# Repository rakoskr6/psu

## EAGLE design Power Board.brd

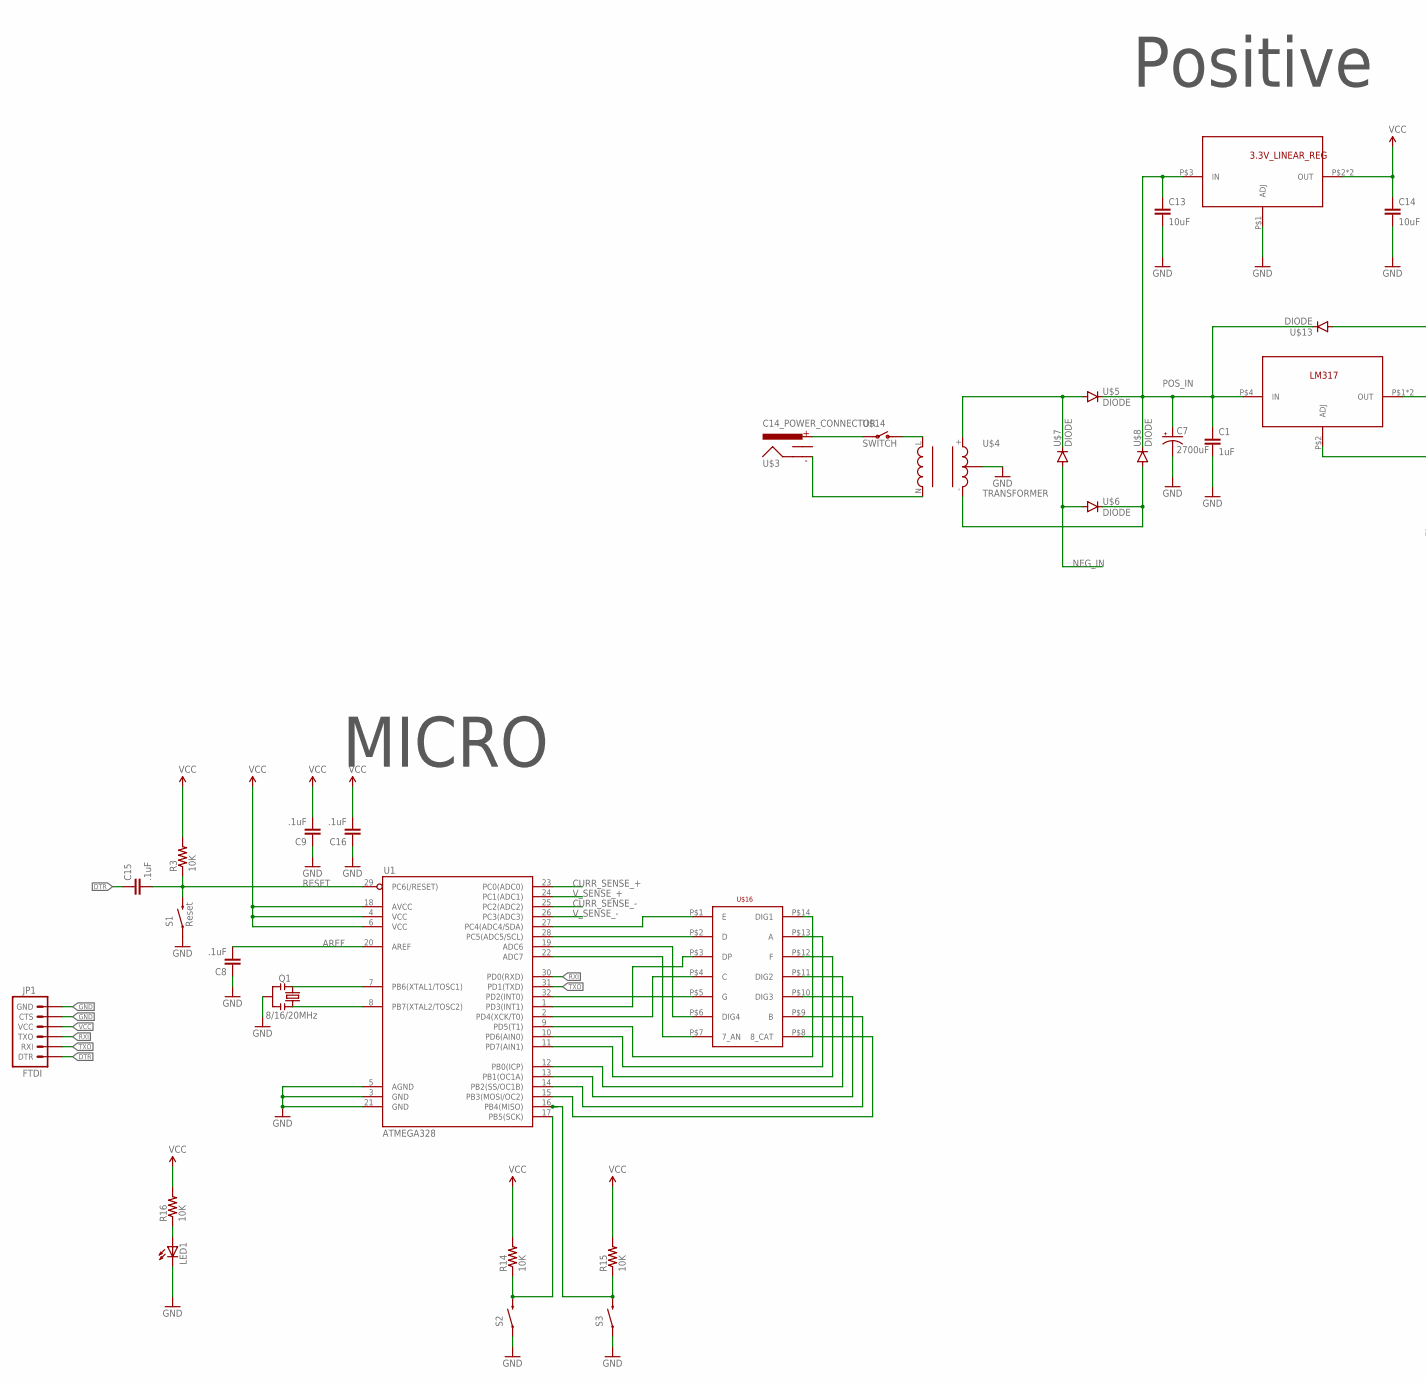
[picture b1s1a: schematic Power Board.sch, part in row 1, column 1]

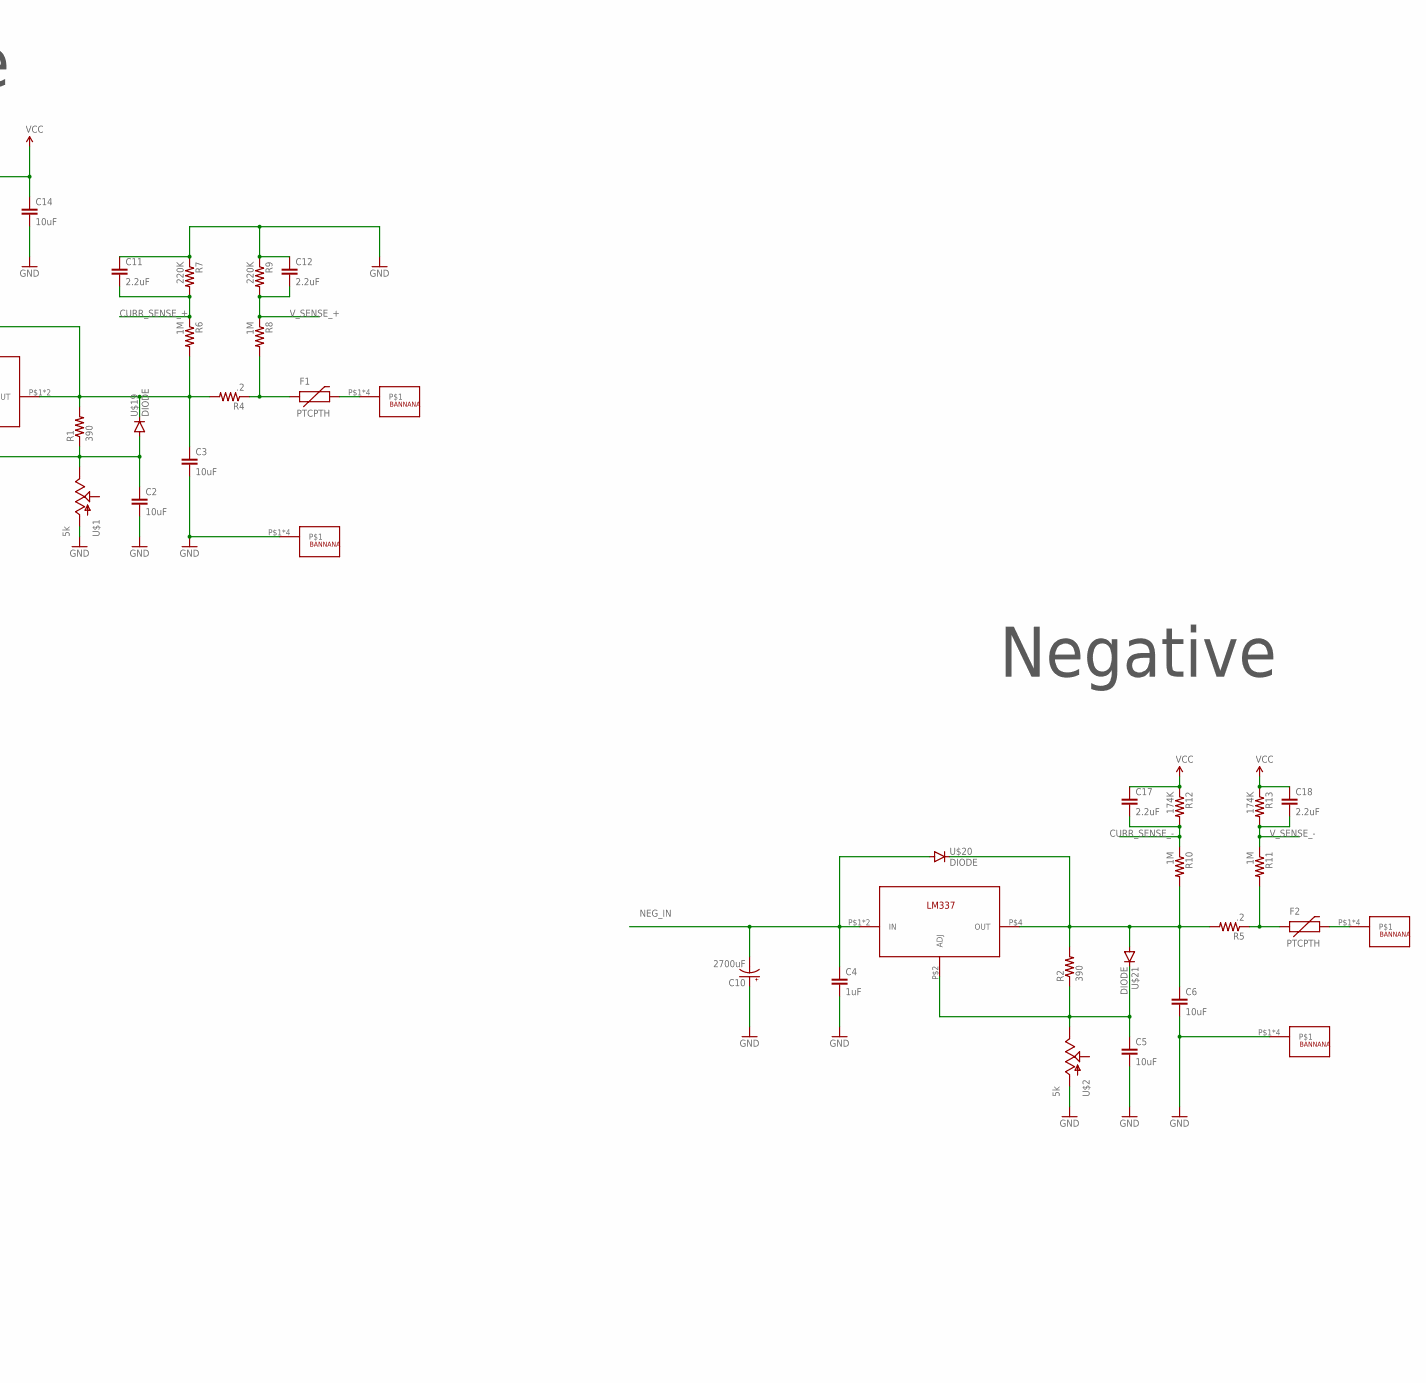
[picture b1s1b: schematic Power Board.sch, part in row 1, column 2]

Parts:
3.3V_LINEAR_REG: 3.3_LIN_REG; 3.3_LINEAR_REG
C1, C4: 1uF; 1206
C2, C3, C5, C6, C13, C14: 10uF; 1206
C7, C10: 2700uF; CPOL-RADIAL-1000UF-63V
C8, C9, C15, C16: .1uF; 1206
C11, C12, C17, C18: 2.2uF; 1206
F1, F2: PTCPTH; PTC
JP1: FTDI; 1X06
LED1: LED1206; LED-1206
LM317: LM317; KTT
LM337: LM337; KTT
NEG-GND: BANNANA
NEG-OUT: BANNANA
POS-GND: BANNANA
POS-OUT: BANNANA
Q1: 8/16/20MHz; RESONATOR-SMD-1:1
R1, R2: 390; 1206
R3, R14, R15, R16: 10K; 1206
R4, R5: .2; 1206
R6, R8, R10, R11: 1M; 1206
R7, R9: 220K; 1206
R12, R13: 174K; 1206
S1, S2, S3: Reset; TACTILE-SWITCH-SMD-ALT01
U1: ATMEGA328; TQFP32-08
U$1, U$2: 5k; POT
U$3: C14_POWER_CONNECTOR; PANEL_FOR_POWER
U$4: TRANSFORMER
U$5, U$6, U$7, U$8, U$13, U$19, U$20, U$21: DIODE
U$14: SWITCH
U$16: 4-DIGIT_7_SEG; 4-DIGIT_7-SEG

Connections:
3.3V: C17.1, C18.1, R12.1, R13.1, R15.2
AREF: C8.2, U1.20 (AREF)
CURR_SENSE_+: C11.2, R6.1, R7.2, U1.23 (PC0(ADC0))
CURR_SENSE_-: C17.2, R10.1, R12.2, U1.25 (PC2(ADC2))
CURR_SENS_-: C6.1, LM337.P$4 (OUT), R2.2, R5.2, R10.2, U$20.C, U$21.A
CUR_SENS_+: C3.1, LM317.P$1 (OUT), LM317.P$3 (OUT), R1.2, R4.2, R6.2, U$13.A, U$19.C
DTR: C15.1, JP1.1 (DTR)
GND: 3.3V_LINEAR_REG.P$1 (ADJ), C1.2, C2.2, C3.2, C4.2, C5.2, C6.2, C7.2 (-), C8.1, C9.1, C10.1 (+), C11.1, C12.1, C13.2, C14.2, C16.1, JP1.5 (CTS), JP1.6 (GND), LED1.C, NEG-GND.P$1, NEG-GND.P$2, NEG-GND.P$3, NEG-GND.P$4, POS-GND.P$1, POS-GND.P$2, POS-GND.P$3, POS-GND.P$4, Q1.2, R7.1, R9.1, S1.1, S1.2 (1), S2.1, S2.2 (1), S3.1, S3.2 (1), U1.3 (GND), U1.5 (AGND), U1.21 (GND), U$1.P$1 (A), U$2.P$1 (A), U$4.GND (4)
unnamed: U$3.P$3 (LINE), U$14.P$3
unnamed: U$3.P$1 (NEUTRAL), U$4.N (2)
unnamed: U$4.+ (5), U$5.A, U$7.C
unnamed: U1.9 (PD5(T1)), U$16.P$14 (DIG1)
unnamed: U$4.- (3), U$6.C, U$8.A
unnamed: U1.27 (PC4(ADC4/SDA)), U$16.P$1 (E)
unnamed: LED1.A, R16.1
unnamed: C2.1, LM317.P$2 (ADJ), R1.1, U$1.P$3 (E), U$19.A
unnamed: U1.28 (PC5(ADC5/SCL)), U$16.P$2 (D)
unnamed: Q1.3, U1.8 (PB7(XTAL2/TOSC2))
unnamed: U1.19 (ADC6), U$16.P$6 (DIG4)
unnamed: C5.1, LM337.P$2 (ADJ), R2.1, U$2.P$3 (E), U$21.C
unnamed: Q1.1, U1.7 (PB6(XTAL1/TOSC1))
unnamed: U1.22 (ADC7), U$16.P$7 (7_AN)
unnamed: U1.32 (PD2(INT0)), U$16.P$5 (G)
unnamed: U1.13 (PB1(OC1A)), U$16.P$10 (DIG3)
unnamed: U1.10 (PD6(AIN0)), U$16.P$13 (A)
unnamed: U1.11 (PD7(AIN1)), U$16.P$12 (F)
unnamed: U1.12 (PB0(ICP)), U$16.P$11 (DIG2)
unnamed: U1.14 (PB2(SS/OC1B)), U$16.P$9 (B)
unnamed: U1.15 (PB3(MOSI/OC2)), U$16.P$8 (8_CAT)
unnamed: U1.2 (PD4(XCK/T0)), U$16.P$4 (C)
unnamed: F1.P$2 (2), POS-OUT.P$1, POS-OUT.P$2, POS-OUT.P$3, POS-OUT.P$4
unnamed: F2.P$2 (2), NEG-OUT.P$1, NEG-OUT.P$2, NEG-OUT.P$3, NEG-OUT.P$4
unnamed: U$4.L (1), U$14.P$4 (O)
unnamed: U1.1 (PD3(INT1)), U$16.P$3 (DP)
unnamed: R15.1, S3.3 (2), S3.4 (2), U1.16 (PB4(MISO))
NEG_IN: C4.1, C10.2 (-), LM337.P$1 (IN), LM337.P$3 (IN), U$6.A, U$7.A, U$20.A
POS_IN: 3.3V_LINEAR_REG.P$3 (IN), C1.1, C7.1 (+), C13.1, LM317.P$4 (IN), U$5.C, U$8.C, U$13.C
RESET: C15.2, R3.1, S1.3 (2), S1.4 (2), U1.29 (PC6(/RESET))
RESET1: R14.1, S2.3 (2), S2.4 (2), U1.17 (PB5(SCK))
RXI: JP1.3 (TXO), U1.30 (PD0(RXD))
TXO: JP1.2 (RXI), U1.31 (PD1(TXD))
VCC: 3.3V_LINEAR_REG.P$2 (OUT), 3.3V_LINEAR_REG.P$4 (OUT), C9.2, C14.1, C16.2, JP1.4 (VCC), R3.2, R14.2, R16.2, U1.4 (VCC), U1.6 (VCC), U1.18 (AVCC)
V_SENSE_+: C12.2, R8.1, R9.2, U1.24 (PC1(ADC1))
V_SENSE_-: C18.2, R11.1, R13.2, U1.26 (PC3(ADC3))
V_SENS_+: F1.P$1 (1), R4.1, R8.2
V_SENS_-: F2.P$1 (1), R5.1, R11.2

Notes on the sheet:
MICRO
Negative
Positive

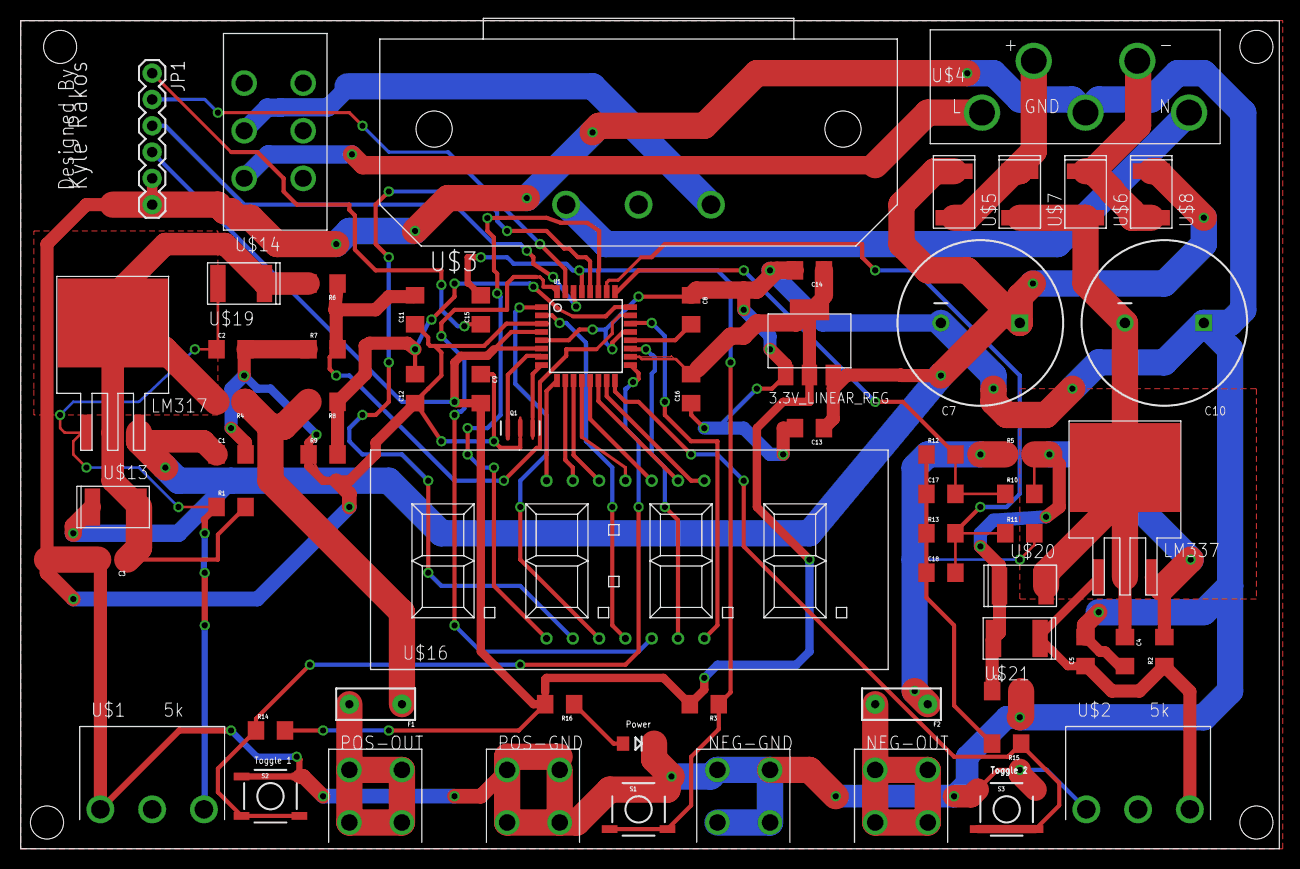
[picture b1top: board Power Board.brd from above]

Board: 2 copper layers, 121.6 x 80.0 mm, 64 parts (0 on the bottom side), 46 nets.

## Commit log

2016-08-07 Initial boards
2016-08-07 Initial layout
2016-08-14 Initial board layout placement
2016-08-14 Started traces
2016-08-15 Finished routing
2016-08-15 Some fixes, and Gerbers
2016-08-24 planes added
2016-10-02 Removed Arduino boards
2016-10-02 Some part updates and rerouting

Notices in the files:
parts and their libraries:
SparkFun-Capacitors: Licensing: Creative Commons ShareAlike 4.0 International - https://creativecommons.org/licenses/by-sa/4.0
